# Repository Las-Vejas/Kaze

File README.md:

<h1 align="center">
  <br>
  
  <br>
  <sub>Kaze</sub>
  <br>
</h1>

<div align="center">

</div>

<h4 align="center">An all-in-one ambient sensor for <a href="https://www.home-assistant.io/">Home Assistant</a>, powered by the ESP32-C6.</h4>

<br>

## Overview

Kaze is a compact ambient sensor that measures a wide range of environmental data and exposes it to Home Assistant via ESPHome. It supports **Zigbee, Wi-Fi, Bluetooth, and Thread** out of the box thanks to the ESP32-C6 module.

## Sensors

| Sensor | Measurements |
|--------|-------------|
| BME680 | Temperature, Humidity, Pressure, CO₂ / AQI |
| TSL25911FN | Illuminance (lux), IR |
| WS2812B | RGB status LED |

## Connectivity

The ESP32-C6-MINI-1 module provides:
- Wi-Fi
- Bluetooth 5
- Thread / Matter
- Zigbee

These will be utilised to connect to your Home Assistant setup and provide temperature readings.

## Software

Firmware is written for **ESPHome**, making it seamless to integrate with Home Assistant. *(Work in progress)*

## Images

## Bill of Materials

### JLCPCB

| Item | Cost |
|------|------|
| PCB (5×) | $2.10 |
| Stencil | $7.00 |
| Shipping (Global Standard Direct Line) | $26.55 |

### LCSC Components

| Part | Mfr. | Qty | Unit Price | Ext. Price | LCSC# |
|------|------|-----|------------|------------|-------|
| ESP32-C6-MINI-1-N4 | Espressif | 2 | $4.04 | $8.09 | [C5736265](https://www.lcsc.com/product-detail/C5736265.html) |
| BME680 | Bosch | 1 | $9.85 | $9.85 | [C125972](https://www.lcsc.com/product-detail/C125972.html) |
| TSL25911FN | AMS | 3 | $1.81 | $5.42 | [C176812](https://www.lcsc.com/product-detail/C176812.html) |
| MCP73831T-2ACI/OT | Microchip | 2 | $0.73 | $1.46 | [C424093](https://www.lcsc.com/product-detail/C424093.html) |
| AP2112K-3.3TRG1 (LDO 3.3V) | Tech Public | 5 | $0.09 | $0.47 | [C23380830](https://www.lcsc.com/product-detail/C23380830.html) |
| WS2812B-2020 (RGB LED) | Worldsemi | 10 | $0.08 | $0.83 | [C965555](https://www.lcsc.com/product-detail/C965555.html) |
| USB-C Receptacle 16P | Shou Han | 20 | $0.06 | $1.20 | [C2765186](https://www.lcsc.com/product-detail/C2765186.html) |
| Tactile Switch SPST | Alps Alpine | 5 | $0.13 | $0.65 | [C115357](https://www.lcsc.com/product-detail/C115357.html) |
| Cap 100nF 0402 | Samsung EM | 100 | $0.005 | $0.49 | [C16193311](https://www.lcsc.com/product-detail/C16193311.html) |
| Cap 4.7µF 0402 | Samsung EM | 20 | $0.009 | $0.18 | [C318563](https://www.lcsc.com/product-detail/C318563.html) |
| Cap 10µF 0402 | Samsung EM | 50 | $0.012 | $0.59 | [C3902158](https://www.lcsc.com/product-detail/C3902158.html) |
| Cap 1µF 16V 0402 | Samsung EM | 100 | $0.002 | $0.23 | [C29266](https://www.lcsc.com/product-detail/C29266.html) |
| Cap 1µF 10V 0402 | Samsung EM | 100 | $0.002 | $0.18 | [C14445](https://www.lcsc.com/product-detail/C14445.html) |
| Res 10kΩ 0402 | Yageo | 100 | $0.001 | $0.07 | [C60489](https://www.lcsc.com/product-detail/C60489.html) |
| Res 4.7kΩ 0402 | Yageo | 100 | $0.001 | $0.07 | [C105870](https://www.lcsc.com/product-detail/C105870.html) |
| Res 2.4kΩ 0402 | Yageo | 100 | $0.001 | $0.07 | [C137889](https://www.lcsc.com/product-detail/C137889.html) |
| Res 5.1kΩ 0402 | Yageo | 100 | $0.001 | $0.08 | [C105872](https://www.lcsc.com/product-detail/C105872.html) |
| Res 22Ω 0402 | Yageo | 100 | $0.001 | $0.07 | [C114765](https://www.lcsc.com/product-detail/C114765.html) |

### Other

| Item | Cost |
|------|------|
| LiPo Battery 3.7V 800mAh (802540) | $6.52 |
| LCSC Shipping | $9.50 |

### 💰 Total Cost Estimate

| | |
|---|---|
| LCSC components + shipping | ~$38.00 |
| JLCPCB PCB + stencil + shipping | ~$35.65 |
| Battery | $6.52 |
| Discounts | −$5.10 |
| **Total** | **~$76.67** |

> Shipping cost for JLCPCB can be roughly halved if ordered alongside another project.

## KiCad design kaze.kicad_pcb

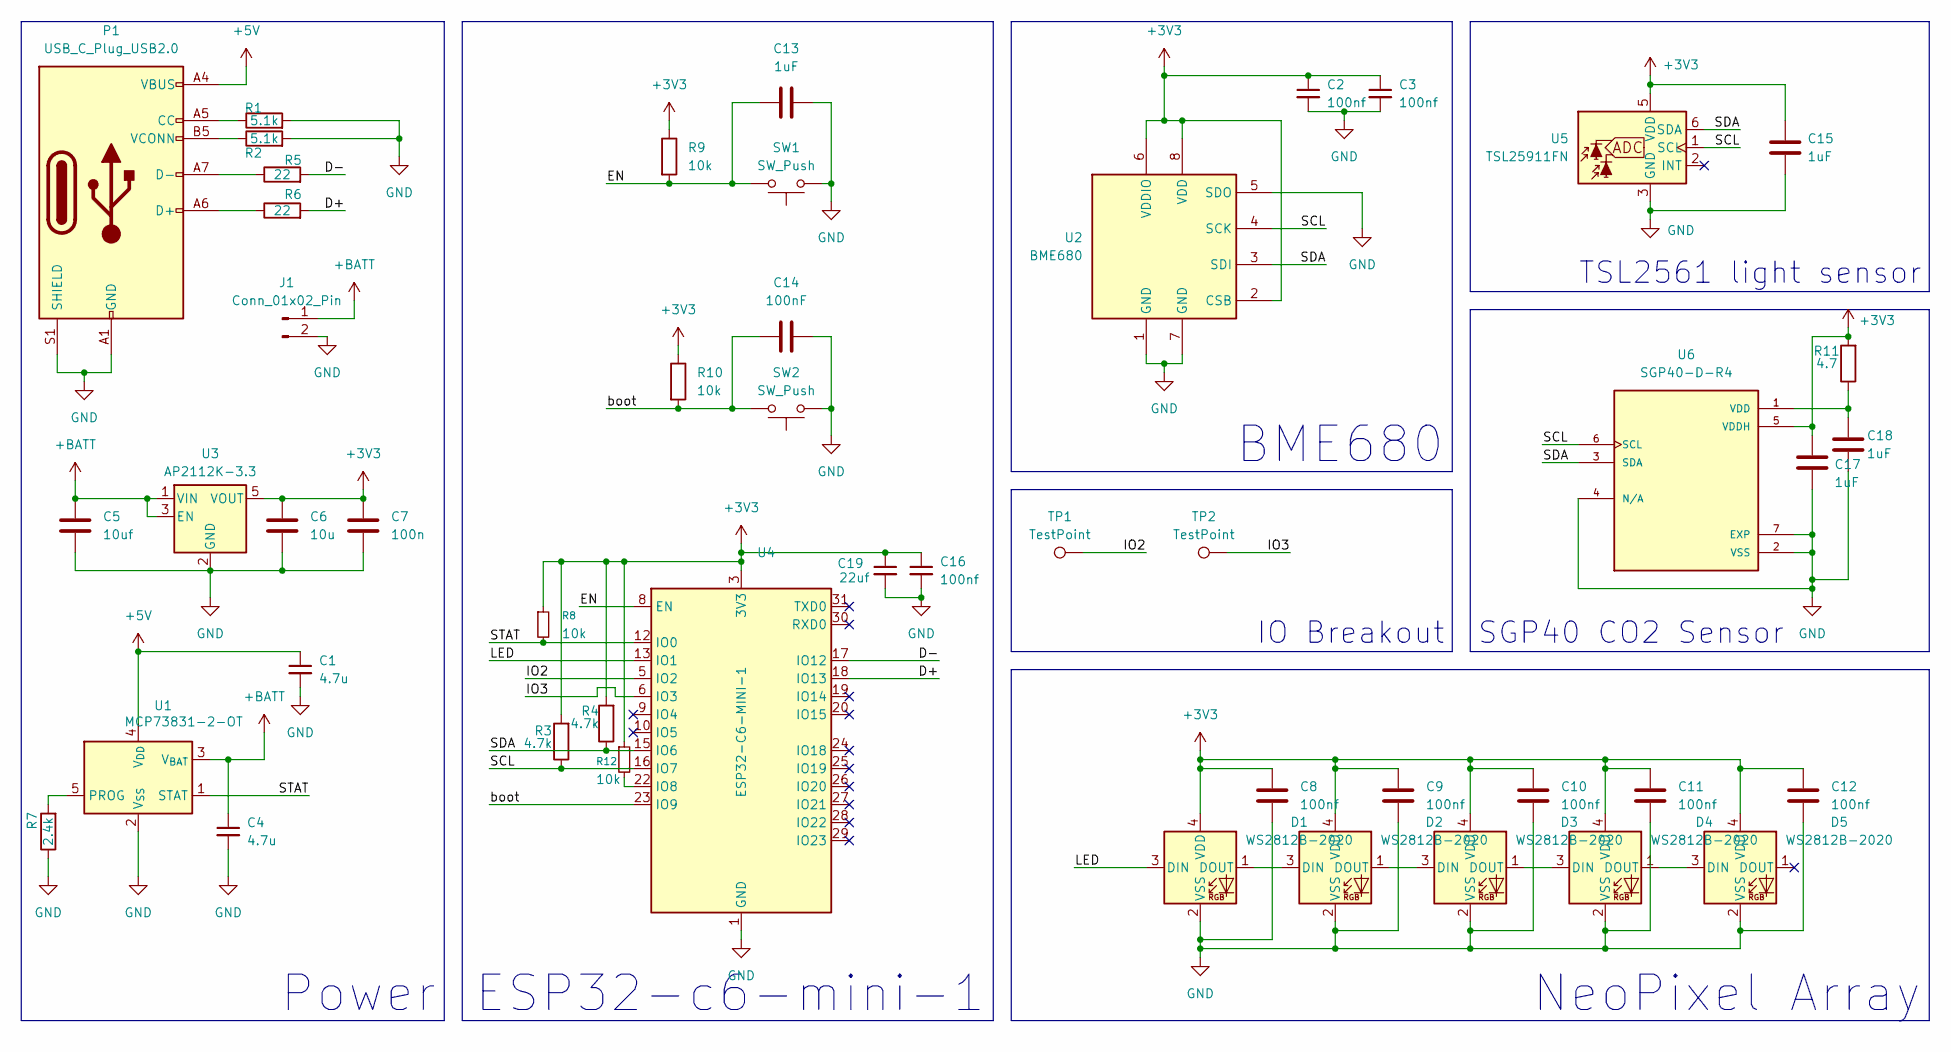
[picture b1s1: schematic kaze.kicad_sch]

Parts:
C1, C4: 4.7u; C_0402_1005Metric
C2, C3, C8, C9, C10, C11, C12, C16: 100nf; C_0402_1005Metric
C5: 10uf; C_0402_1005Metric
C6: 10u; C_0402_1005Metric
C7: 100n; C_0402_1005Metric
C13, C15, C17, C18: 1uF; C_0402_1005Metric
C14: 100nF; C_0402_1005Metric
C19: 22uf; C_0402_1005Metric
D1, D2, D3, D4, D5: WS2812B-2020; LED_WS2812B-2020_PLCC4_2.0x2.0mm
J1: Conn_01x02_Pin; PinHeader_2x01_P1.00mm_Vertical
P1: USB_C_Plug_USB2.0; USB_C_Receptacle_GCT_USB4105-xx-A_16P_TopMnt_Horizontal
R1, R2: 5.1k; R_0402_1005Metric
R3, R4: 4.7k; R_0402_1005Metric
R5, R6: 22; R_0402_1005Metric
R7: 2.4k; R_0402_1005Metric
R8, R9, R10, R12: 10k; R_0402_1005Metric
R11: 4.7; R_0402_1005Metric
SW1, SW2: SW_Push; SW_Push_SPST_NO_Alps_SKRK
TP1, TP2: TestPoint; TestPoint_Pad_D3.0mm
U1: MCP73831-2-OT; SOT-23-5
U2: BME680; Bosch_LGA-8_3x3mm_P0.8mm_ClockwisePinNumbering
U3: AP2112K-3.3; SOT-23-5
U4: ESP32-C6-MINI-1
U5: TSL25911FN; AMS_TSL25911FN
U6: SGP40-D-R4; XCDR_SGP40-D-R4; PARTREV 1.2

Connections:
+3V3: C2.1, C3.1, C6.1, C7.1, C8.1, C9.1, C10.1, C11.1, C12.1, C15.1, C16.1, C17.1, C19.1, D1.4 (VDD), D2.4 (VDD), D3.4 (VDD), D4.4 (VDD), D5.4 (VDD), R3.2, R4.2, R8.1, R9.1, R10.1, R11.2, R12.1, U2.2 (CSB), U2.6 (VDDIO), U2.8 (VDD), U3.5 (VOUT), U4.3 (3V3), U5.5 (VDD), U6.5 (VDDH); also elsewhere on the board
+5V: C1.1, P1.A4 (VBUS), P1.A9 (VBUS), P1.B4 (VBUS), P1.B9 (VBUS), U1.4 (V_{DD})
+BATT: C4.1, C5.1, J1.1, U1.3 (V_{BAT}), U3.1 (VIN), U3.3 (EN)
/D+: R6.2, U4.18 (IO13)
/D-: R5.2, U4.17 (IO12)
/EN: C13.1, R9.2, SW1.2, U4.8 (EN); also elsewhere on the board
/IO2: TP1.1, U4.5 (IO2); also elsewhere on the board
/IO3: TP2.1, U4.6 (IO3); also elsewhere on the board
/LED: D1.3 (DIN), U4.13 (IO1)
/SCL: R3.1, U2.4 (SCK), U4.16 (IO7), U5.1 (SCL), U6.6 (SCL)
/SDA: R4.1, U2.3 (SDI), U4.15 (IO6), U5.6 (SDA), U6.3 (SDA)
/STAT: R8.2, U1.1 (STAT), U4.12 (IO0)
/boot: C14.1, R10.2, SW2.2, U4.23 (IO9)
GND: C1.2, C2.2, C3.2, C4.2, C5.2, C6.2, C7.2, C8.2, C9.2, C10.2, C11.2, C12.2, C13.2, C14.2, C15.2, C16.2, C17.2, C18.2, C19.2, D1.2 (VSS), D2.2 (VSS), D3.2 (VSS), D4.2 (VSS), D5.2 (VSS), J1.2, P1.A1 (GND), P1.A12 (GND), P1.B1 (GND), P1.B12 (GND), P1.S1 (SHIELD), R1.2, R2.2, R7.1, SW1.1, SW2.1, U1.2 (V_{SS}), U2.1 (GND), U2.5 (SDO), U2.7 (GND), U3.2 (GND), U4.1 (GND), U4.2 (GND), U4.11 (GND), U4.14 (GND), U4.36 (GND), U4.37 (GND), U4.38 (GND), U4.39 (GND), U4.40 (GND), U4.41 (GND), U4.42 (GND), U4.43 (GND), U4.44 (GND), U4.45 (GND), U4.46 (GND), U4.47 (GND), U4.48 (GND), U4.49 (GND), U4.50 (GND), U4.51 (GND), U4.52 (GND), U4.53 (GND), U5.3 (GND), U6.2 (VSS), U6.4 (N/A), U6.7 (EXP)
unnamed: D1.1 (DOUT), D2.3 (DIN)
unnamed: D2.1 (DOUT), D3.3 (DIN)
unnamed: D3.1 (DOUT), D4.3 (DIN)
unnamed: D4.1 (DOUT), D5.3 (DIN)
unnamed: P1.A5 (CC), R1.1
unnamed: P1.A6 (D+), R6.1
unnamed: P1.A7 (D-), R5.1
unnamed: P1.B5 (VCONN), R2.1
unnamed: R7.2, U1.5 (PROG)
unnamed: R12.2, U4.22 (IO8)
unnamed: C18.1, R11.1, U6.1 (VDD)

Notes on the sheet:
TSL2561 light sensor
ESP32-c6-mini-1
NeoPixel Array
IO Breakout
SGP40 CO2 Sensor
Power
BME680

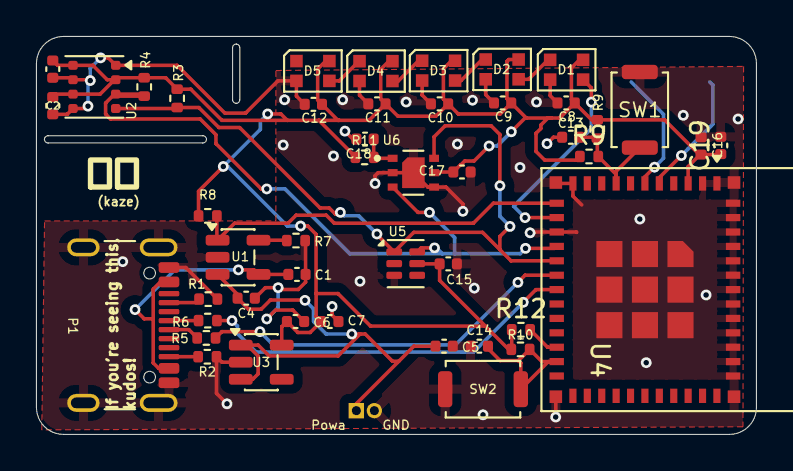
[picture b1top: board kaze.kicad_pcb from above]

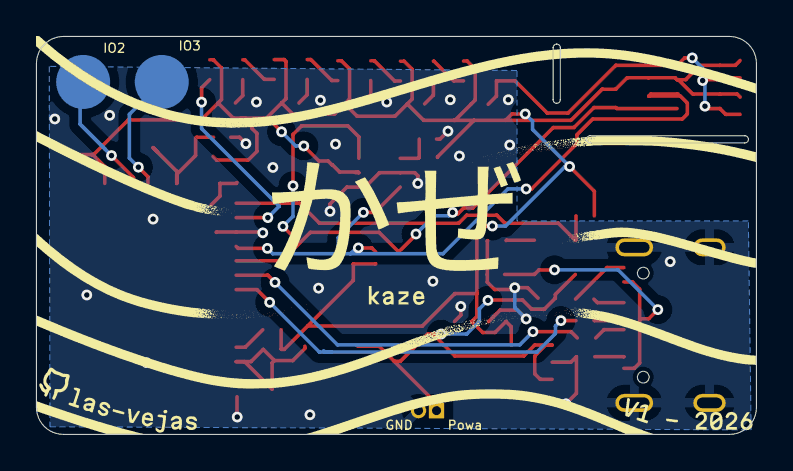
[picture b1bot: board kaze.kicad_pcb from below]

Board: 2 copper layers, 40.0 x 22.1 mm, 49 parts (2 on the bottom side), 25 nets.

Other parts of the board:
IO2, IO3: TestPoint; TestPoint_Pad_D3.0mm
R9#2: 10k; R_0402_1005Metric

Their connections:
+3V3: R9#2.1; also elsewhere on the board
/EN: R9#2.2; also elsewhere on the board
/IO2: IO2.1; also elsewhere on the board
/IO3: IO3.1; also elsewhere on the board

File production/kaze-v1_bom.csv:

Designator,Footprint,Quantity,Value,LCSC Part #
"C1, C4",0402,2,4.7u,
"C10, C11, C12, C14, C16, C2, C3, C8, C9",0402,9,100nf,
"C13, C15, C17, C18",0402,4,1uF,
C19,0402,1,22uf,
C5,0402,1,10uf,
C6,0402,1,10u,
C7,0402,1,100n,
"D1, D2, D3, D4, D5",LED_WS2812B-2020_PLCC4_2.0x2.0mm,5,WS2812B-2020,
"IO2, IO3",TestPoint_Pad_D3.0mm,2,TestPoint,
J1,PinHeader_2x01_P1.00mm_Vertical,1,Conn_01x02_Pin,
P1,USB_C_Receptacle_GCT_USB4105-xx-A_16P_TopMnt_Horizontal,1,USB_C_Plug_USB2.0,
"R1, R2",0402,2,5.1k,
"R10, R12, R8, R9_2, R9",0402,5,10k,
R11,0402,1,4.7,
"R3, R4",0402,2,4.7k,
"R5, R6",0402,2,22,
R7,0402,1,2.4k,
"SW1, SW2",SW_Push_SPST_NO_Alps_SKRK,2,SW_Push,
U1,SOT-23-5,1,MCP73831-2-OT,
U2,Bosch_LGA-8_3x3mm_P0.8mm_ClockwisePinNumbering,1,BME680,
U3,SOT-23-5,1,AP2112K-3.3,
U4,ESP32-C6-MINI-1,1,ESP32-C6-MINI-1,
U5,AMS_TSL25911FN,1,TSL25911FN,
U6,XCDR_SGP40-D-R4,1,SGP40-D-R4,

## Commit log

2026-01-10 stuffs
2026-01-10 Revise README with new project name and features
    Updated project name and added detailed description of features and capabilities.
2026-01-28 Update README with BOM details and component links
    Added BOM tables for JLCPCB and LCSC components with pricing and links.
2026-02-17 Add project motivation to README
    Added a personal motivation statement for the project.
2026-04-25 Revise README with project overview and BOM
    Updated the README to include an overview, detailed sensor information, connectivity options, and a bill of materials with cost estimates.
2026-04-27 Update README to include links for badges
2026-04-27 Fix badge link formatting in README.md
